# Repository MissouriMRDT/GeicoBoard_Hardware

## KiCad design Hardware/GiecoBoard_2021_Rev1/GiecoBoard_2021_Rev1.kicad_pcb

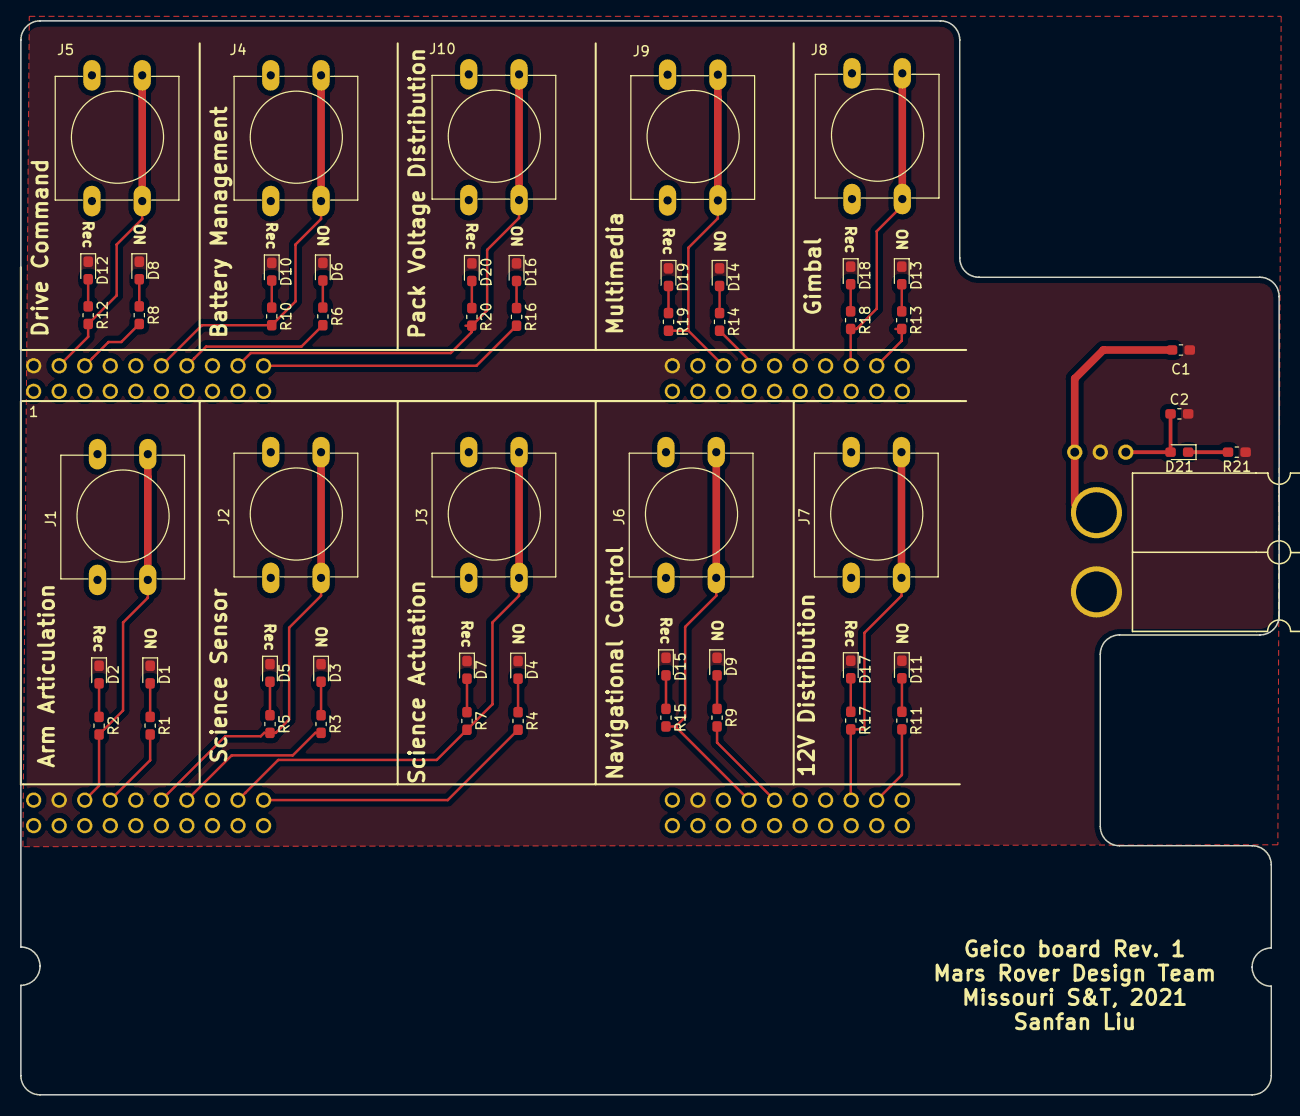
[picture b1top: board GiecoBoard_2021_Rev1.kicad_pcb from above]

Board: 2 copper layers, 125.1 x 106.8 mm, 57 parts (1 on the bottom side), 44 nets.

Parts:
C1, C2: 10uF; C_0603_1608Metric_Pad1.05x0.95mm_HandSolder
Conn1: AndersonPP; Anderson_2_Horizontal_Side_by_Side
D1, D3, D4, D6, D8, D9, D11, D13, D14, D16, D21: Green; LED_0603_1608Metric_Pad1.05x0.95mm_HandSolder
D2, D5, D7, D10, D12, D15, D17, D18, D19, D20: Blue; LED_0603_1608Metric_Pad1.05x0.95mm_HandSolder
J1, J2, J3, J4, J5, J6, J7, J8, J9, J10: Conn_02x02_Top_Bottom; SW_PUSH-12mm
R1, R2, R3, R4, R5, R6, R7, R8, R9, R10, R11, R12, R13, R14, R15, R16, R17, R18, R19, R20, R21: 330; R_0603_1608Metric_Pad1.05x0.95mm_HandSolder
U1: TM4C129E_Launchpad; TM4C129E_Launchpad_FULL_THT_BOTTOM
U2: OKI; OKI_Horizontal

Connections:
+3V3: C2.1, D21.2, J1.1, J2.1, J3.1, J4.1, J5.1, J6.1, J7.1, J8.1, J9.1, J10.1, U1.+3V3, U2.3
GND: C1.2, C2.2, Conn1.1, D1.1, D2.1, D3.1, D4.1, D5.1, D6.1, D7.1, D8.1, D9.1, D10.1, D11.1, D12.1, D13.1, D14.1, D15.1, D16.1, D17.1, D18.1, D19.1, D20.1, R21.1, U1.GND, U2.2
unnamed: C1.1, Conn1.2, U2.1
unnamed: D1.2, R1.1
unnamed: D2.2, R2.1
unnamed: D3.2, R3.1
unnamed: D4.2, R4.1
unnamed: D5.2, R5.1
unnamed: D6.2, R6.1
unnamed: D7.2, R7.1
unnamed: D8.2, R8.1
unnamed: D9.2, R9.1
unnamed: D10.2, R10.1
unnamed: D11.2, R11.1
unnamed: D12.2, R12.1
unnamed: D13.2, R13.1
unnamed: D14.2, R14.1
unnamed: D15.2, R15.1
unnamed: D16.2, R16.1
unnamed: D17.2, R17.1
unnamed: D18.2, R18.1
unnamed: D19.2, R19.1
unnamed: D20.2, R20.1
unnamed: D21.1, R21.2
REC_LED_12VDistribution: R11.2, U1.PA4
REC_LED_ArmArticulation: R1.2, U1.PE1
REC_LED_BatteryManagement: R13.2, U1.PQ1
REC_LED_DriveCommand: R8.2, U1.PH2
REC_LED_Gimbal: R6.2, U1.PD0
REC_LED_Multimedia: R16.2, U1.PP2
REC_LED_NavigationalControl: R9.2, U1.PK0
REC_LED_PackVoltageDistribution: R14.2, U1.PA7
REC_LED_ScienceActuation: R4.2, U1.PM5
REC_LED_ScienceSensor: R3.2, U1.PD7
Send_12VDistribution: J7.2, R17.2, U1.PK3
Send_ArmArticulation: J1.2, R2.2, U1.PE0
Send_BatteryManagement: J8.2, R18.2, U1.PP3
Send_DriveCommand: J5.2, R12.2, U1.PM3
Send_Gimbal: J4.2, R10.2, U1.PD1
Send_Multimedia: J10.2, R20.2, U1.PN3
Send_NavigationalControl: J6.2, R15.2, U1.PB5
Send_PackVoltageDistribution: J9.2, R19.2, U1.PP5
Send_ScienceActuation: J3.2, R7.2, U1.PM4
Send_ScienceSensor: J2.2, R5.2, U1.PE3

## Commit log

2020-09-17 folder and project created
2020-09-17 getting started
2020-09-23 layout
2020-09-23 schematic
2020-09-28 changeLED resistors value
2020-09-28 Annotate and colored LEDs
2020-10-01 1st_BoardReviewChange
2020-10-12 layout_no wiring
2020-10-14 fliped tiva_pin on layout
2020-10-14 wiring on layout
2020-10-21 add edge cuts,silk screen
2020-11-03 fix 3.3v buck
2020-11-17 Layout review update
2020-11-18 change TIVA footprint
2020-11-30 widen the trace
2020-11-30 Post CDR update
2020-11-30 add manufacturer product number
2020-12-01 flip tiva and wiring
2020-12-01 board changes fixed
    -edge cuts corrected
    -andersons changed to horizontal andersons
    -3v3 plane moved where necessary
2020-12-01 update gerb
